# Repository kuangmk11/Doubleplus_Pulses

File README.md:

# Pulses Plus

A performance-oriented gate router for the Music Thing Turing Machine. Eight pulse channels,
each switchable to one of two merge buses or off; each bus computes the OR or the AND of
whatever is routed to it, chosen live from the panel.

**Built and tested.** 8 HP, 128.5 × 40.16 mm.

It sits **alongside** a stock Pulses expander rather than replacing it, taking its signals from
the Turing Machine's 16-pin expander ribbon and passing that ribbon through so other expanders
can still be chained downstream.

The stock Pulses gives you seven fixed outputs plus four hard-wired AND combinations. Those AND
outputs are the musical ones — ANDing two shift-register taps gives a sparser, related rhythm.
This generalises that: any subset of the eight bits, OR'd or AND'd, chosen by hand, live. The
four fixed ANDs become a strict subset of what the switches can do.

---

## What's here

| | |
|---|---|
| `pulses_plus_submin.kicad_sch` | schematic — 87 placed components |
| `pulses_plus_submin.kicad_pcb` | main board |
| **`pulses_plus_submin_panel_v4.kicad_pcb`** | **current panel** |
| `pulses_plus_submin_panel.kicad_pcb` | v1 panel — the geometry source `build_panel.py` inherits holes from |
| `pulses_plus_submin.pretty/` | project footprints — toggle, jack, LED, panel holes |
| `switch_fix.kicad_sym` | the DPDT symbol with the pin numbering the footprint expects |
| `3d/` | 3D models the footprints reference |
| `BOM.md` | bill of materials, DigiKey and JLCPCB/LCSC columns |
| `BOM_DigiKey.csv` | the same BOM as a DigiKey cart upload |
| `gerbers/` | fab packages — see below |
| `tools/build_panel.py` | regenerates the panel artwork |
| `PANEL_STYLE_v1.12.md` | the panel house style |
| `docs/pulses-plus-design.md` | full design write-up, including the diode-leak analysis and why 6 HP was abandoned |
| `docs/sw-t2-4x-b-a2-ma2-data-sheet.pdf` | Taiway 200-MDP3 toggle datasheet |

### Which gerbers to order

`gerbers/` accumulated every revision that was sent out. The panel to order is
`gerbers/panelv4.rar`. For the board:

- **`gerbers_v2/`** — current plot of `pulses_plus_submin_v2.kicad_pcb`, **including C5/C6**
  (see the erratum below). Not yet fabbed.
- **`gerbers/controlv2.zip`** — what was actually fabbed and built. Boards from this package
  predate C5/C6 and need the two-capacitor rework.

The loose `.gbr`/`.drl` files at the top of `gerbers/` are the most recent plot of the
main board and the v1/v2 panels, kept unzipped for inspection.

---

## Erratum — ghost triggers on edge-sensitive gate inputs

**Any board built without C5/C6 needs a two-capacitor rework.**

**Symptom.** On the step *after* a real trigger — a step where the bus should be silent — a
downstream envelope fires an extra time. The bus LED never visibly flashes, and the same envelope
behaves correctly on the Turing Machine's own pulse output and on a stock Pulses. A **Kassutronics
ASR** is the known case; the affected class is any gate input that triggers on the *rising edge* at
a low threshold (the ASR's fires from ~+1.2 V).

**Cause.** The Turing Machine's expander bits are `stage AND clock`, and the clock's rising edge
opens that AND before the shift register has finished shifting — so the ribbon briefly presents the
previous step's pattern. This module's two cascaded CD40106 Schmitt buffers then regenerate that
soft sub-µs bump into a sharp, near-full-amplitude micro-gate. Full analysis in
[`docs/pulses-plus-design.md`](docs/pulses-plus-design.md#stale-bit-glitch-and-edge-sensitive-gate-inputs).

**Fix.** Tack a **4.7 nF** ceramic on top of **R15**, and another on top of **R16**. Those 1206 pads
are already `BUSA_SEL`→GND and `BUSB_SEL`→GND on the back of the board, so there are no trace cuts,
no lifted pins, and it is fully reversible. Verified on hardware.

- **Do not use a smaller value.** 1 nF was measured insufficient; 2.2 nF computes marginal.
- **Multing the output is not a workaround.** It appears to help and then stops helping — cable
  capacitance is an order of magnitude too small to filter this.
- The fix is in the **v2** project files (`pulses_plus_submin_v2.*`) as C5/C6. The v1 files do not
  have it.

## How it works

Each channel's DPDT ON-OFF-ON toggle throws left to bus A, right to bus B, or centre for off.
Both poles are used: pole 1 carries only the OR diodes, pole 2 only the AND diodes. That
separation is the one non-obvious constraint in the design — sharing a pole leaks current
through the unselected bus and pins its OR net high.

Per bus, a second toggle picks OR, MUTE or AND. Both nets are computed continuously and in
parallel, so the mode switch only selects which one reaches the output buffer and the 32 merge
diodes never switch. Centre-off leaves the buffer input pulled low, which is the mute.

The **EXT** jack is switched (normalled): unplugged, buffered BIT8 feeds channel 8; plugged, an
external gate takes its place through a transistor and Schmitt stage that squares up whatever
amplitude arrives.

Full write-up: **[`docs/pulses-plus-design.md`](docs/pulses-plus-design.md)**.

## Using it

The two buses are **two independent reads of the same shift register**. Whatever either one
plays is built from the same eight bits on the same loop, so they cannot drift apart — but give
them different channels, or put one in AND and the other in OR, and they come out at different
densities. Related, never identical. Most of the musical mileage is in that gap.

### Gates on A, note changes on B

The patch this turned out to be best at, and not one it was designed for:

1. **OUT A → your envelope or VCA gate.** A few channels to bus A in **OR** — a busy,
   rhythmic gate stream.
2. **OUT B → a quantizer's trigger or sample input**, with the Turing Machine's CV output
   feeding that quantizer's CV input. A *different*, smaller set of channels to bus B, in
   **AND** for something sparser again.

The quantizer only samples when bus B fires, so the note is **held** across every gate bus A
produces in between. A melody moves on its own slow rhythm while the gates articulate
underneath — and because both rhythms are subsets of one register, the note changes land on
beats the gate pattern already stresses. It reads as a phrase, not as two voices running at
once.

Being a Turing Machine underneath, the loop-length and randomness controls then act on the
whole thing at once: lock the register for a repeating riff, open it a crack and the melody
mutates while staying in its scale.

**Pulse width passes straight through.** The board is purely combinational: it merges what
arrives on the ribbon and never looks at the clock. It does not need to — the Turing Machine's
expander bus already carries each bit ANDed with the clock, so the bits arrive as *pulses*, and
the diode merge preserves their width. Feed the TM a narrow clock and the outputs are narrow;
feed it a wide one and they are wide, all the way to OUT A and OUT B.

So an AND that is true on three consecutive steps gives three pulses, one per step — each
re-triggering the envelope or re-pinging the quantizer, rather than merging into one long gate.
The note changes on every step the condition holds, which is why choosing a condition that comes
true *rarely* is what makes the melody move slowly.

**Things to reach for:**

- **B in AND with two or three channels** is the sweet spot. AND of several bits comes true
  rarely, which is what you want from a melody that moves every few bars rather than every step.
- **MUTE on B** freezes the pitch without touching the gate pattern — drop the melody in and
  out by hand mid-take. That is what the centre position is for.
- **The EXT jack earns its keep here.** Patch an outside rhythm into channel 8 and AND it into
  bus B, and the note only changes where your own pattern and the Turing Machine agree —
  a melody keyed to something the TM knows nothing about.
- An **AND bus with nothing routed to it sits high**, held there by its 10k pull-up rather than
  driven by any bit, so it never pings anything. Route at least one channel to a bus you want
  triggers from.

## Key parts

10 × Taiway 200-MDP3 sub-miniature DPDT ON-OFF-ON toggles (ø4.95 bushing), 2 × CD4050 buffers,
1 × CD40106 Schmitt, 33 × 1N4148, 10 × 3 mm LEDs, 3 × Thonkiconn jacks — **J3 must be the
switched variant** — and 2 × 2×8 IDC headers for ribbon in and thru. See [`BOM.md`](BOM.md).

---

## Panel

The current panel is **v4**, `pulses_plus_submin_panel_v4.kicad_pcb` — white silkscreen on black
soldermask, drawn to [`PANEL_STYLE_v1.12.md`](PANEL_STYLE_v1.12.md).

It is generated. [`tools/build_panel.py`](tools/build_panel.py) reads the v1 panel and regenerates
only the artwork, inheriting every control-hole position, so the style guide's one non-negotiable
rule — hole positions are inherited, never computed — holds by construction rather than by
inspection:

```sh
python3 tools/build_panel.py
```

Mounting is four 6.4 × 3.2 mm obround slots on Edge.Cuts, horizontal for ±1.6 mm of slide.
`kicad-cli pcb drc` reports zero violations. Zones refill on open — refill before plotting.

Reading the panel: a ring means signal leaves there, so the two output jacks are the only closed
circles. `A`/`B` beside each toggle are throw directions, not names. The mode stack is `AND` up,
`MUTE` centre, `OR` down. Names sit below the thing they name.

---

## Related repositories

- **[Doubleplus_Pulses_VCV](https://github.com/kuangmk11/Doubleplus_Pulses_VCV)** — a VCV Rack 2 port
  of this module. It reconstructs the Turing Machine's shift register locally, so it runs without
  the hardware.
- **[Turing-Pulse-Expander](https://github.com/kuangmk11/Turing-Pulse-Expander)** — the archive:
  Tom Whitwell's original Rev 2 expander, plus the superseded studies this design grew out of.

## Licence

CC BY-NC-SA 4.0 — see [`LICENSE`](LICENSE).

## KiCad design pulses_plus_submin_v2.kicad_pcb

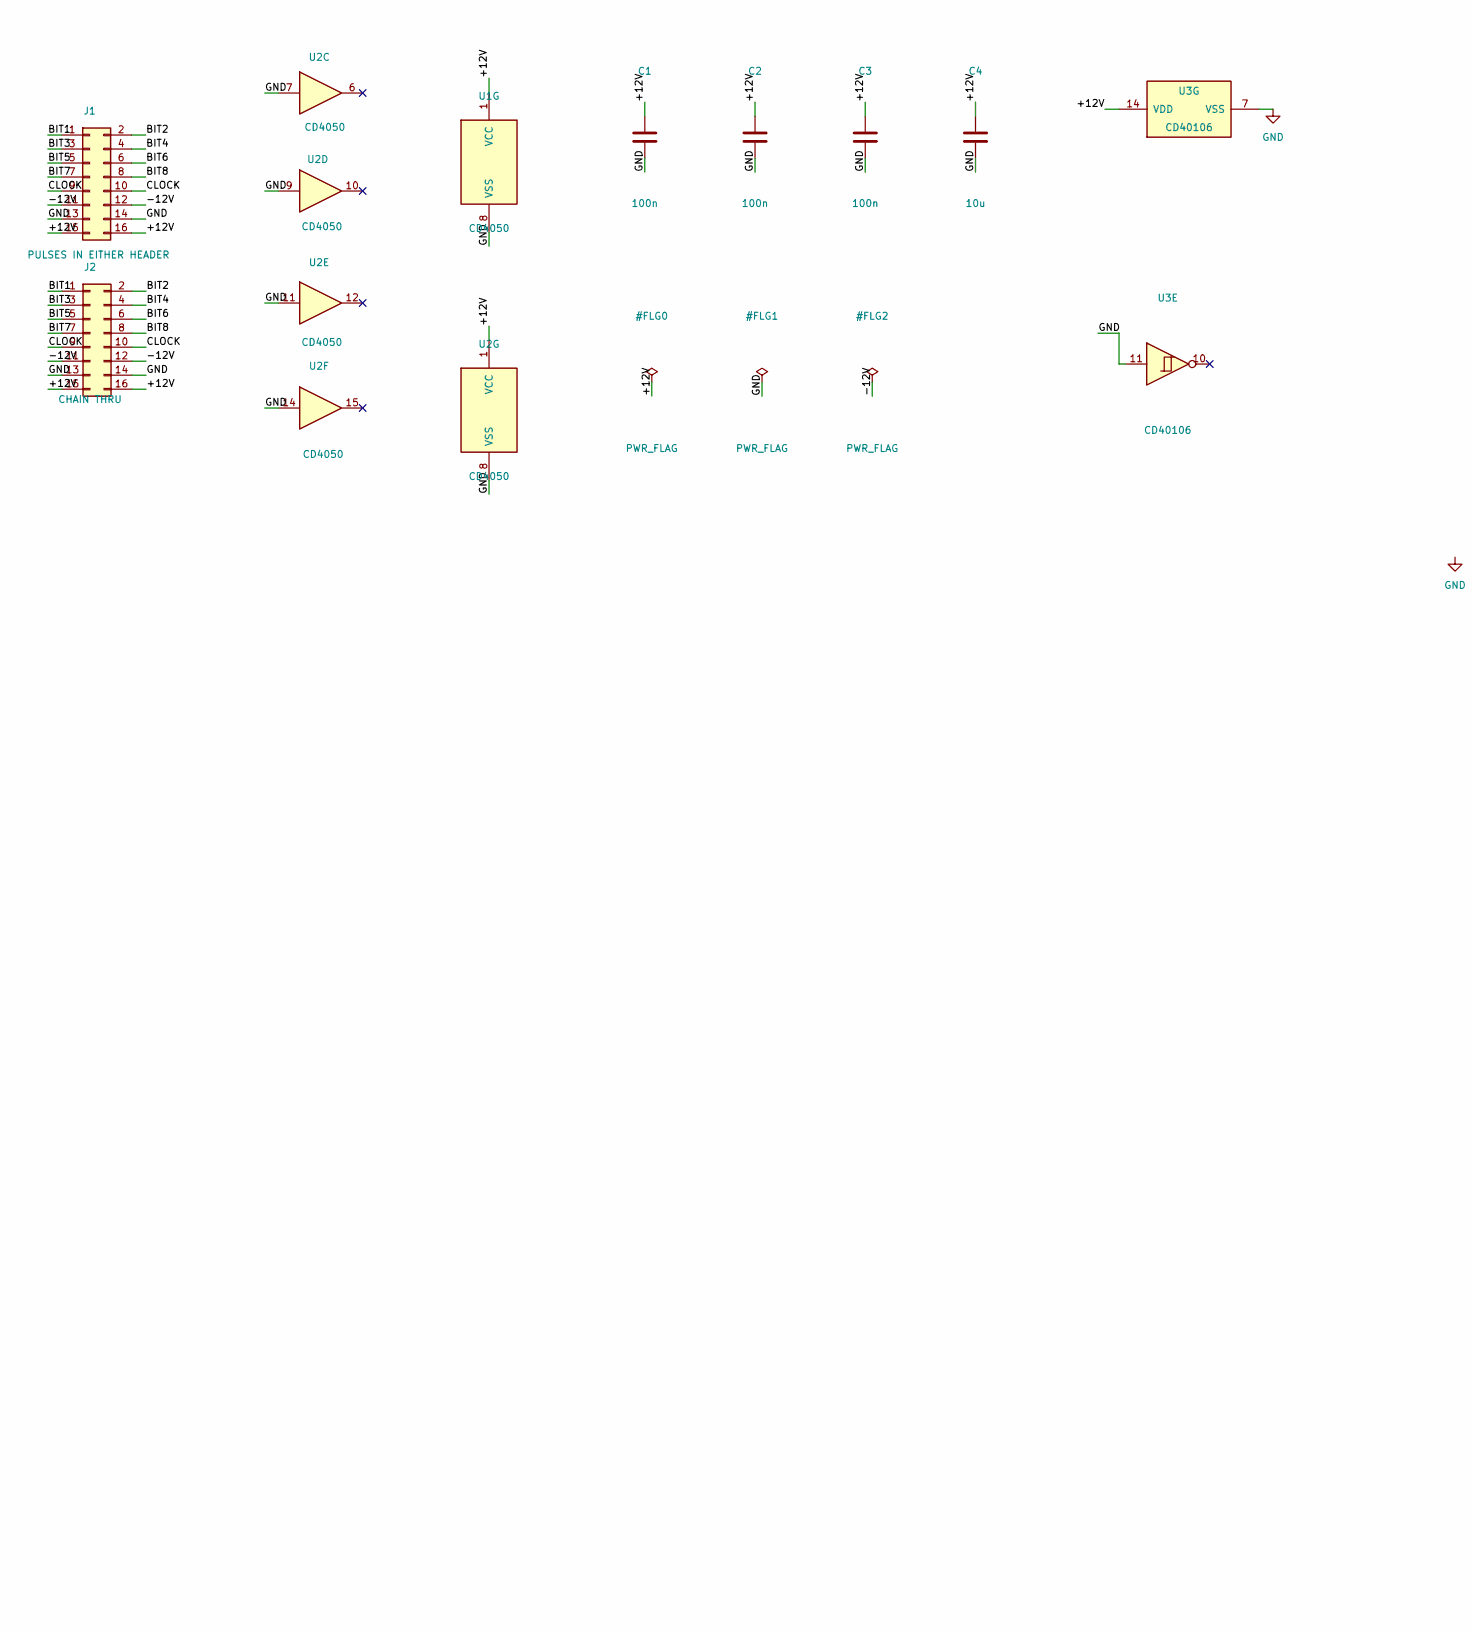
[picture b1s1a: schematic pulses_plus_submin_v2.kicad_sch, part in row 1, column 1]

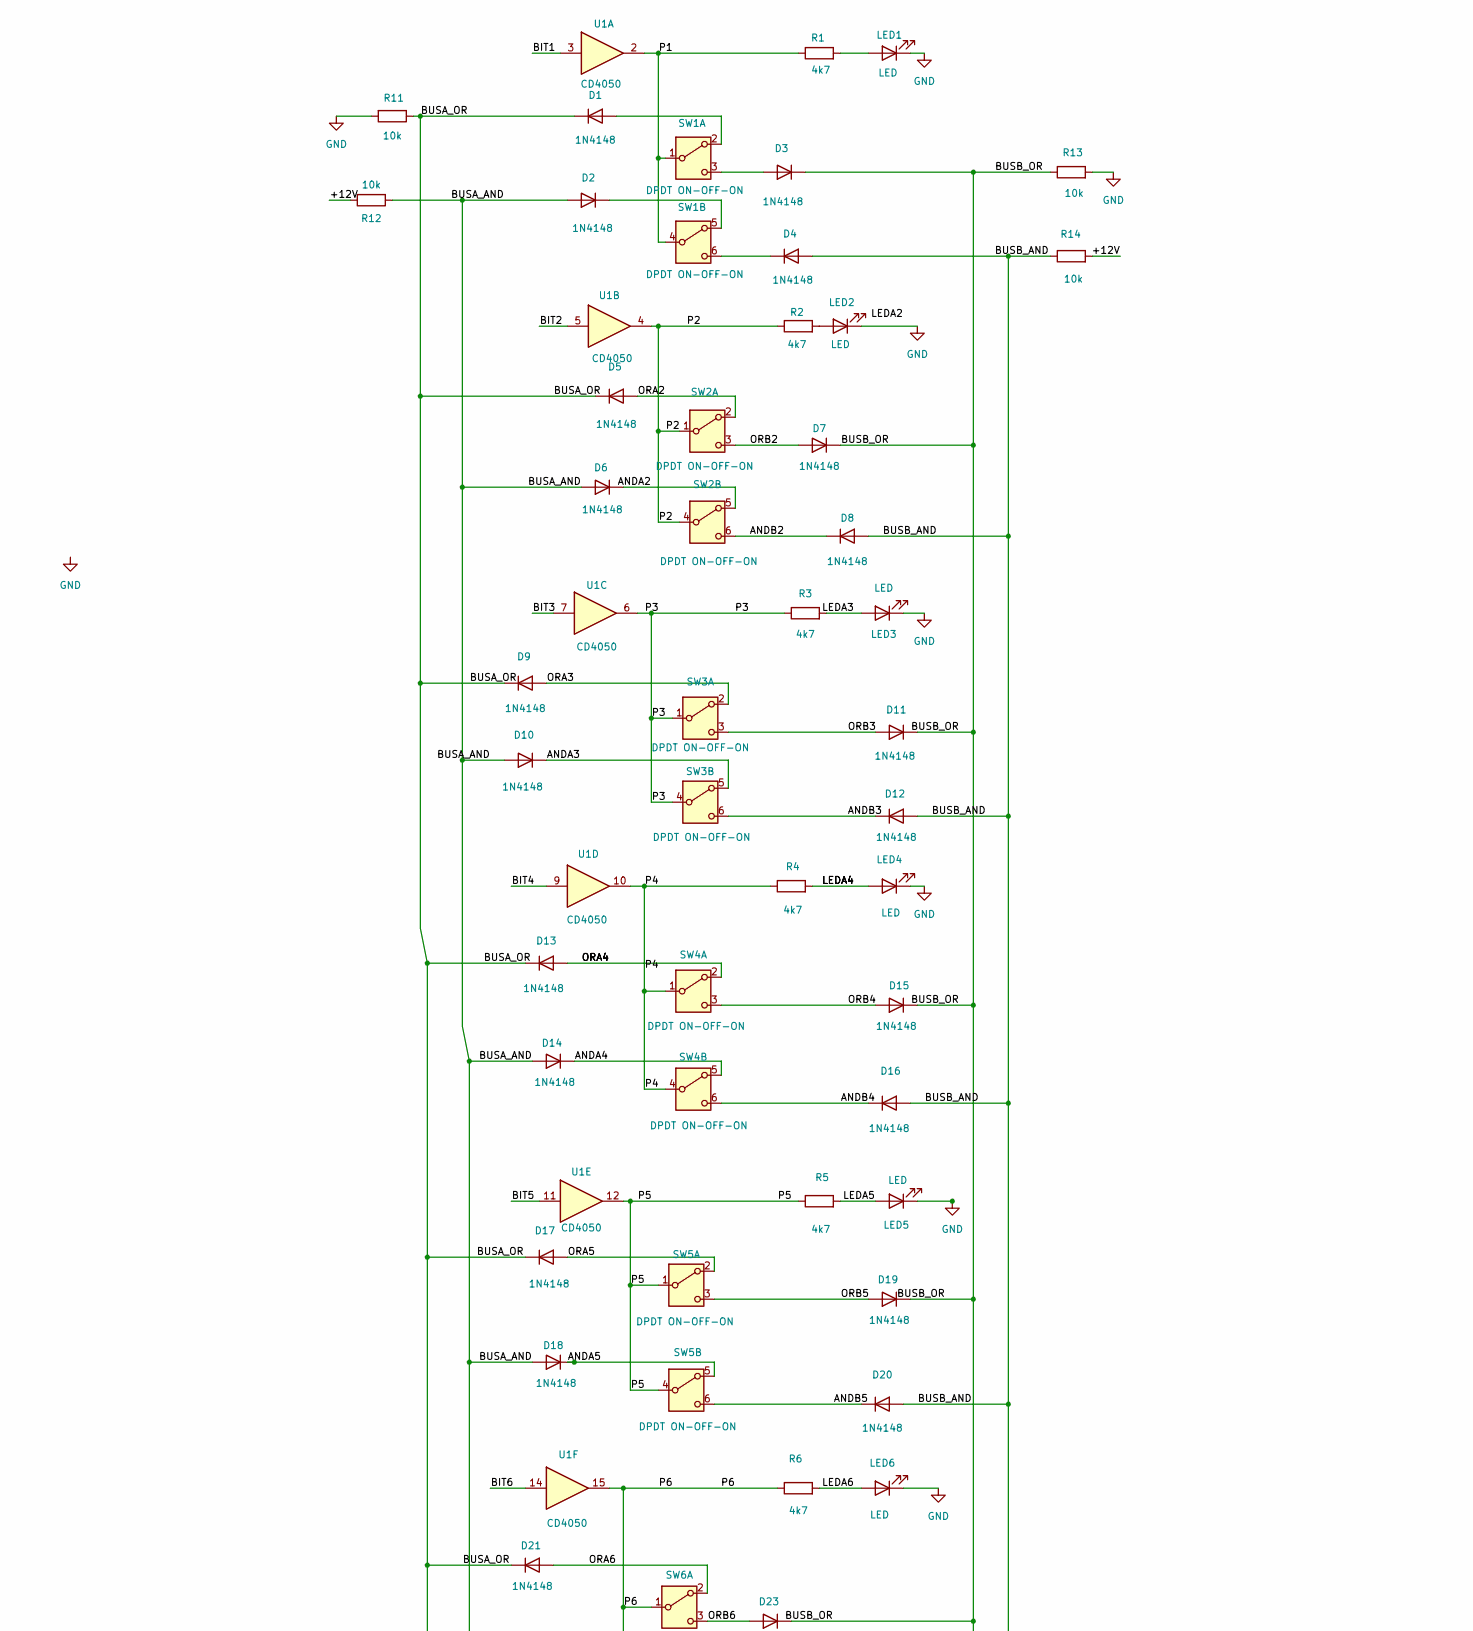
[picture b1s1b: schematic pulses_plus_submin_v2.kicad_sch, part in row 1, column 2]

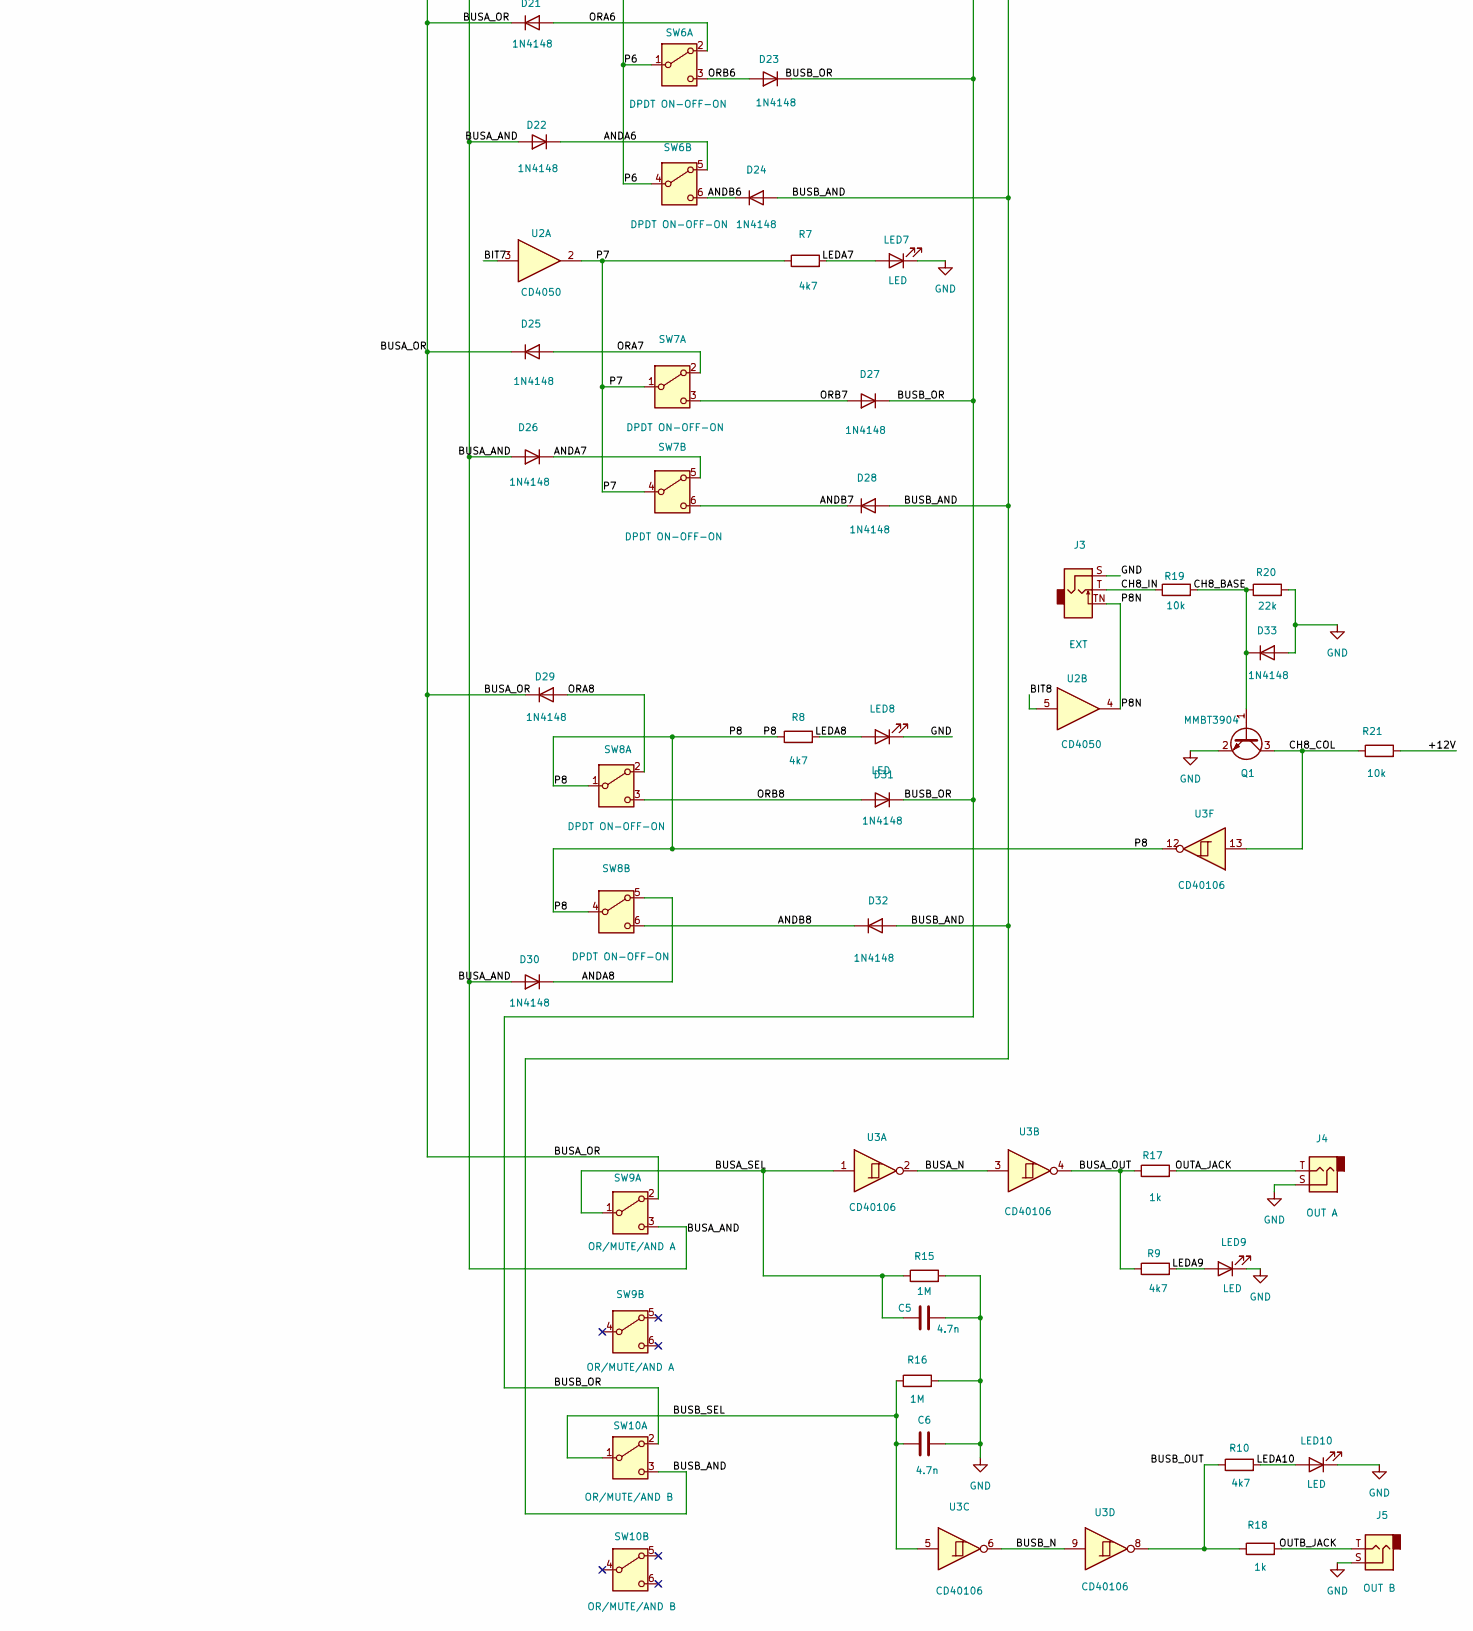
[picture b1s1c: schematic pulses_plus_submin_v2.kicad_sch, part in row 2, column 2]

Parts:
C1, C2, C3: 100n; C_1206_3216Metric_Pad1.33x1.80mm_HandSolder
C4: 10u; C_1206_3216Metric_Pad1.33x1.80mm_HandSolder
C5, C6: 4.7n; C_1206_3216Metric_Pad1.33x1.80mm_HandSolder
D1, D2, D3, D4, D5, D6, D7, D8, D9, D10, D11, D12, D13, D14, D15, D16, D17, D18, D19, D20, D21, D22, D23, D24, D25, D26, D27, D28, D29, D30, D31, D32, D33: 1N4148; D_SOD-123
J1: PULSES IN EITHER HEADER; IDC-Header_2x08_P2.54mm_Vertical
J2: CHAIN THRU; IDC-Header_2x08_P2.54mm_Vertical
J3: EXT; Thonkiconn_PJ301M
J4: OUT A; Thonkiconn_PJ301M
J5: OUT B; Thonkiconn_PJ301M
LED1, LED2, LED3, LED4, LED5, LED6, LED7, LED8, LED9, LED10: LED; LED_D3.0mm
Q1: MMBT3904; SOT-23
R1, R2, R3, R4, R5, R6, R7, R8, R9, R10: 4k7; R_1206_3216Metric_Pad1.30x1.75mm_HandSolder
R11, R12, R13, R14, R19, R21: 10k; R_1206_3216Metric_Pad1.30x1.75mm_HandSolder
R15, R16: 1M; R_1206_3216Metric_Pad1.30x1.75mm_HandSolder
R17, R18: 1k; R_1206_3216Metric_Pad1.30x1.75mm_HandSolder
R20: 22k; R_1206_3216Metric_Pad1.30x1.75mm_HandSolder
SW1, SW2, SW3, SW4, SW5, SW6, SW7, SW8: DPDT ON-OFF-ON; SW_200_MDP3_DPDT
SW9: OR/MUTE/AND A; SW_200_MDP3_DPDT
SW10: OR/MUTE/AND B; SW_200_MDP3_DPDT
U1, U2: CD4050; DIP-16_W7.62mm
U3: CD40106; DIP-14_W7.62mm

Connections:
/+12V: C1.1, C2.1, C3.1, C4.1, J1.15, J1.16, J2.15, J2.16, R12.2, R14.2, R21.2, U1.1 (VCC), U2.1 (VCC), U3.14 (VDD)
/-12V: J1.11, J1.12, J2.11, J2.12
/ANDA2: D6.1 (K), SW2.5 (B)
/ANDA3: D10.1 (K), SW3.5 (B)
/ANDA4: D14.1 (K), SW4.5 (B)
/ANDA5: D18.1 (K), SW5.5 (B)
/ANDA6: D22.1 (K), SW6.5 (B)
/ANDA7: D26.1 (K), SW7.5 (B)
/ANDA8: D30.1 (K), SW8.5 (B)
/ANDB2: D8.1 (K), SW2.6 (C)
/ANDB3: D12.1 (K), SW3.6 (C)
/ANDB4: D16.1 (K), SW4.6 (C)
/ANDB5: D20.1 (K), SW5.6 (C)
/ANDB6: D24.1 (K), SW6.6 (C)
/ANDB7: D28.1 (K), SW7.6 (C)
/ANDB8: D32.1 (K), SW8.6 (C)
/BIT1: J1.1, J2.1, U1.3
/BIT2: J1.2, J2.2, U1.5
/BIT3: J1.3, J2.3, U1.7
/BIT4: J1.4, J2.4, U1.9
/BIT5: J1.5, J2.5, U1.11
/BIT6: J1.6, J2.6, U1.14
/BIT7: J1.7, J2.7, U2.3
/BIT8: J1.8, J2.8, U2.5
/BUSA_AND: D2.2 (A), D6.2 (A), D10.2 (A), D14.2 (A), D18.2 (A), D22.2 (A), D26.2 (A), D30.2 (A), R12.1, SW9.3 (C)
/BUSA_N: U3.2, U3.3
/BUSA_OR: D1.1 (K), D5.1 (K), D9.1 (K), D13.1 (K), D17.1 (K), D21.1 (K), D25.1 (K), D29.1 (K), R11.1, SW9.2 (B)
/BUSA_OUT: R9.1, R17.1, U3.4
/BUSB_AND: D4.2 (A), D8.2 (A), D12.2 (A), D16.2 (A), D20.2 (A), D24.2 (A), D28.2 (A), D32.2 (A), R14.1, SW10.3 (C)
/BUSB_N: U3.6, U3.9
/BUSB_OR: D3.1 (K), D7.1 (K), D11.1 (K), D15.1 (K), D19.1 (K), D23.1 (K), D27.1 (K), D31.1 (K), R13.1, SW10.2 (B)
/BUSB_OUT: R10.1, R18.1, U3.8
/CH8_BASE: D33.1 (K), Q1.1 (B), R19.2, R20.1
/CH8_COL: Q1.3 (C), R21.1, U3.13
/CH8_IN: J3.T, R19.1
/CLOCK: J1.9, J1.10, J2.9, J2.10
/LEDA3: LED3.2 (A), R3.2
/LEDA5: LED5.2 (A), R5.2
/LEDA6: LED6.2 (A), R6.2
/LEDA7: LED7.2 (A), R7.2
/LEDA8: LED8.2 (A), R8.2
/LEDA9: LED9.2 (A), R9.2
/LEDA10: LED10.2 (A), R10.2
/ORA2: D5.2 (A), SW2.2 (B)
/ORA3: D9.2 (A), SW3.2 (B)
/ORA5: D17.2 (A), SW5.2 (B)
/ORA6: D21.2 (A), SW6.2 (B)
/ORA7: D25.2 (A), SW7.2 (B)
/ORA8: D29.2 (A), SW8.2 (B)
/ORB2: D7.2 (A), SW2.3 (C)
/ORB3: D11.2 (A), SW3.3 (C)
/ORB4: D15.2 (A), SW4.3 (C)
/ORB5: D19.2 (A), SW5.3 (C)
/ORB6: D23.2 (A), SW6.3 (C)
/ORB7: D27.2 (A), SW7.3 (C)
/ORB8: D31.2 (A), SW8.3 (C)
/OUTA_JACK: J4.T, R17.2
/OUTB_JACK: J5.T, R18.2
/P1: R1.1, SW1.1 (A), SW1.4 (A), U1.2
/P2: R2.1, SW2.1 (A), SW2.4 (A), U1.4
/P3: R3.1, SW3.1 (A), SW3.4 (A), U1.6
/P4: R4.1, SW4.1 (A), SW4.4 (A), U1.10
/P5: R5.1, SW5.1 (A), SW5.4 (A), U1.12
/P6: R6.1, SW6.1 (A), SW6.4 (A), U1.15
/P7: R7.1, SW7.1 (A), SW7.4 (A), U2.2
/P8: R8.1, SW8.1 (A), SW8.4 (A), U3.12
/P8N: J3.TN, U2.4
GND: C1.2, C2.2, C3.2, C4.2, C5.2, C6.2, D33.2 (A), J1.13, J1.14, J2.13, J2.14, J3.S, J4.S, J5.S, LED1.1 (K), LED2.1 (K), LED3.1 (K), LED4.1 (K), LED5.1 (K), LED6.1 (K), LED7.1 (K), LED8.1 (K), LED9.1 (K), LED10.1 (K), Q1.2 (E), R11.2, R13.2, R15.2, R16.2, R20.2, U1.8 (VSS), U2.7, U2.8 (VSS), U2.9, U2.11, U2.14, U3.7 (VSS), U3.11
unnamed: D1.2 (A), SW1.2 (B)
unnamed: D2.1 (K), SW1.5 (B)
unnamed: D3.2 (A), SW1.3 (C)
unnamed: D4.1 (K), SW1.6 (C)
unnamed: D13.2 (A), SW4.2 (B)
unnamed: LED1.2 (A), R1.2
unnamed: LED2.2 (A), R2.2
unnamed: LED4.2 (A), R4.2

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
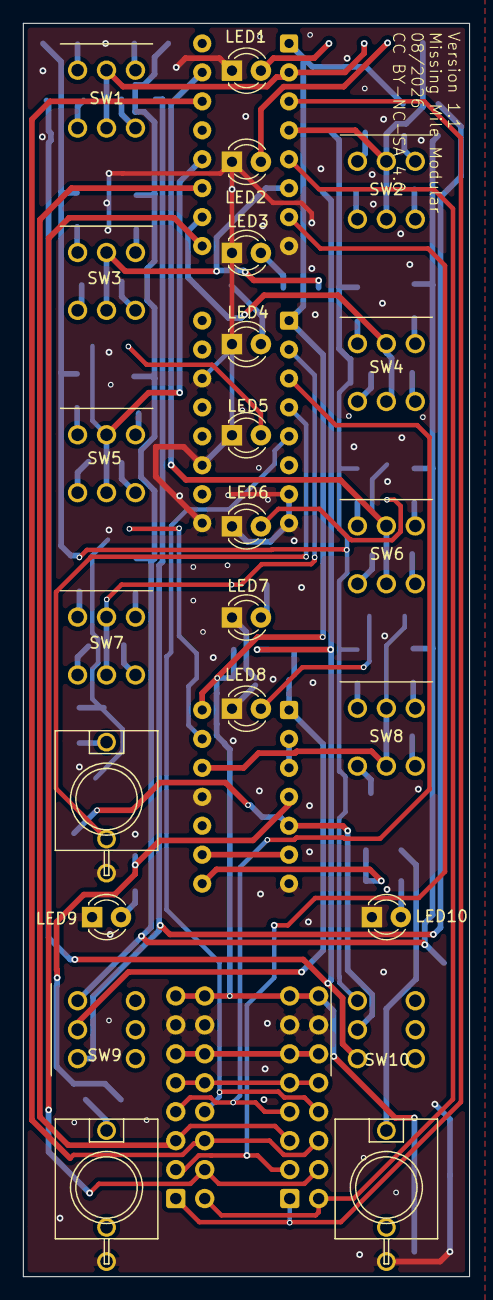
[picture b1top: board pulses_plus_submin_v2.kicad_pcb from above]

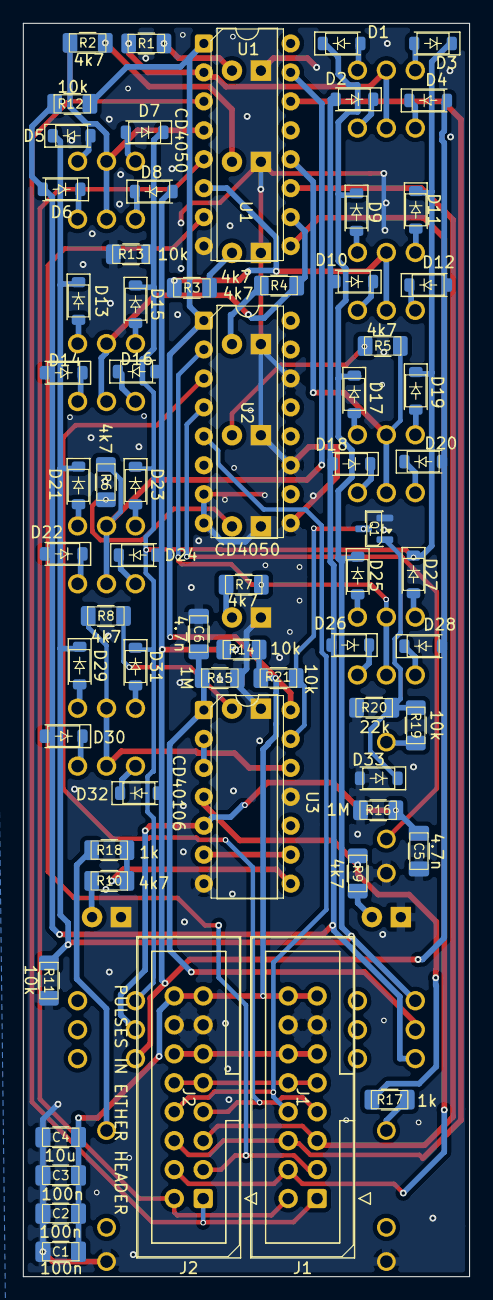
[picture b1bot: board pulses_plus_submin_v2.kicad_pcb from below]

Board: 2 copper layers, 39.2 x 110.0 mm, 89 parts (66 on the bottom side), 78 nets.

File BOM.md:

# Pulses Plus (sub-mini) — Bill of Materials

Generated from `pulses_plus_submin_v2.kicad_sch` (89 placed components, 19 line items).
Two sourcing columns:

- **DigiKey** — for hand assembly (the THT parts and jacks are hand-solder anyway).
- **JLCPCB / LCSC** — the LCSC `C`-number is what JLCPCB SMT assembly needs for the SMD parts.

Switches are sourced from **Love My Switches** (they are the Taiway 200 sub-mini toggles,
not a DigiKey/LCSC stock part).

> ⚠ **Verify before ordering** — part numbers marked *(verify)* are the correct manufacturer
> series but the exact distributor SKU / LCSC stock C-number should be confirmed against live
> stock at order time. Confirmed numbers came from distributor listings and are noted as such.

---

## BOM table

| # | Qty | Value | Refs | Package / Footprint | Mfr Part | DigiKey | JLCPCB / LCSC |
|---|-----|-------|------|---------------------|----------|---------|---------------|
| 1 | 10 | **DPDT ON-OFF-ON toggle** | SW1–SW10 | Taiway 200 sub-mini, PC vertical, ø4.95 bushing | Taiway **200-MDP3-T2B1M2QE** | — | — |
| 2 | 2 | CD4050 hex buffer | U1, U2 | DIP-16 | **CD4050BE** (TI) | 296-2056-ND | C(verify) |
| 3 | 1 | CD40106 hex Schmitt | U3 | DIP-14 | **CD40106BE** (TI) | 296-9797-5-ND *(verify)* | **C71251** |
| 4 | 1 | MMBT3904 NPN | Q1 | SOT-23 | **MMBT3904** | MMBT3904FSCT-ND | **C20526** |
| 5 | 33 | 1N4148 switching diode | D1–D33 | SOD-123 (`Diode_SMD:D_SOD-123`) | **1N4148W** | 1N4148W-FDICT-ND | **C81598** |
| 6 | 10 | 4k7 resistor | R1–R10 | 1206, 1% | Yageo **RC1206FR-074K7L** | search mfr PN | C(verify) |
| 7 | 6 | 10k resistor | R11–R14, R19, R21 | 1206, 1% | Yageo **RC1206FR-0710KL** | search mfr PN | C(verify) |
| 8 | 2 | 1k resistor | R17, R18 | 1206, 1% | Yageo **RC1206FR-071KL** | search mfr PN | C(verify) |
| 9 | 1 | 22k resistor | R20 | 1206, 1% | Yageo **RC1206FR-0722KL** | search mfr PN | C(verify) |
| 10 | 2 | 1M resistor | R15, R16 | 1206, 1% | Yageo **RC1206FR-071ML** | search mfr PN | C(verify) |
| 11 | 3 | 100n capacitor | C1, C2, C3 | 1206, X7R, 50V | Samsung **CL31B104KBCNNNC** | 1276-1092-1-ND *(verify)* | C(verify) |
| 12 | 1 | 10µ capacitor | C4 | 1206, X5R, 25V | Samsung **CL31A106KBHNNNE** | 1276-1940-1-ND *(verify)* | C(verify) |
| 13 | 10 | 3mm LED, high-brightness | LED1–LED10 | 3mm THT | e.g. Kingbright WP710A10 series | any 3mm LED | — |
| 14 | 3 | 3.5mm mono jack "Thonkiconn" | J3 (EXT, switched), J4 (OUT A), J5 (OUT B) | PJ301M-12 / PJ398SM | **PJ398SM** | not stocked | not stocked |
| 15 | 2 | 2×8 IDC box header, 2.54mm | J1 (PULSES IN), J2 (CHAIN THRU) | shrouded, vertical | generic 2x8 IDC | 2×8 shrouded header | C(verify) |
| 16 | 2 | **4.7n capacitor** | C5, C6 | 1206, X7R, 50V | Samsung **CL31B472KBCNNNC** *(verify)* | search mfr PN | C(verify) |

**C5/C6 are the glitch filter** — 4.7 nF from each mode-switch common (`BUSA_SEL` / `BUSB_SEL`)
to GND, sitting across R15/R16. They are not decoupling and not optional: without them the module
passes a sub-µs stale-bit spike from the Turing Machine's expander bus through its Schmitt output
buffers, which false-triggers edge-sensitive gate inputs (a Kassutronics ASR is the known case).
**Do not substitute 1 n or 2.2 n** — 1 n was measured insufficient and 2.2 n computes marginal. See
the design doc's *Stale-bit glitch* section.

**J3 must be the switched (normalling) variant** — its break contact normals buffered BIT8 into
channel 8. J4/J5 are plain mono. All three are the same Thonkiconn body.

---

## Sourcing notes

**Switches (SW1–SW10) — Love My Switches**
Taiway **200-MDP3-T2B1M2QE**, "Sub-Mini DPDT On-Off-On, PCB Mount, Short Shaft."
~$2.15 ea (≈ $21.50 for 10). Body 8.1 × 23.2 mm, ships with two nuts + a washer.
Product page: <https://lovemyswitches.com/taiway-sub-mini-dpdt-on-off-on-sw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
Panel hole is ø4.95 mm (10-48 UNS bushing). All 10 switches are this one part.

**Thonkiconn jacks (J3/J4/J5)** — not a DigiKey/LCSC catalog part. Buy from Thonk, Love My
Switches, Synthrotek, or Oddvolt (PJ398SM / PJ301M-12; the two are interchangeable). If you want
JLCPCB to place them, you'll need to supply them as a consigned part or substitute a catalog jack
with the same footprint.

**Resistors** — Yageo RC1206 series part numbers above are deterministic (`RC1206FR-07` + value
code + `L`, F = 1%). Any 1206 thick-film at 1% is fine; values are non-critical. On JLCPCB these
are Basic parts — pick the in-stock C-number for each value in the parts tool.

**Ceramics** — 100n/10µ 1206 X7R/X5R; any reputable 1206 MLCC works. The Samsung CL31 series
numbers are representative JLCPCB Basic parts.

---

## Action items before fab

1. **Diode footprint — RESOLVED in the v2 project.** All 33 diodes (D1–D33) are on
   `Diode_SMD:D_SOD-123`, part **1N4148W / C81598 / DK 1N4148W-FDICT-ND**, in *both*
   `pulses_plus_submin_v2.kicad_sch` and `pulses_plus_submin_v2.kicad_pcb` — verified by inspection,
   so *Update PCB from Schematic* no longer reverts them to 1206. Nets intact (8 diodes per bus,
   pad 1 = K → bus/GND, pad 2 = A).
   > ⚠ The **v1** files (`pulses_plus_submin.kicad_sch`) still carry the old 1206 footprint fields.
   > Work in the v2 project.

2. **Meter the switch** — confirm centre pin = common on the actual Taiway part before committing
   to a board run (design open-question #1). Everything assumes centre-is-common.

3. **LED polarity/brightness** — footprint pad 1 = cathode → GND, pad 2 = anode → 4k7. Use
   modern high-brightness 3mm LEDs (drive is only ~2 mA through 4k7 from a CD4050 output at 12 V).

---

## Verified vs. representative

| Confirmed from distributor listings | Representative (confirm at order) |
|---|---|
| Taiway 200-MDP3-T2B1M2QE (Love My Switches) | CD4050BE LCSC C-number |
| CD4050BE — DigiKey 296-2056-ND | CD40106BE DigiKey SKU |
| CD40106BE — LCSC C71251 | all passive LCSC C-numbers |
| MMBT3904 — LCSC C20526 | ceramic cap DigiKey SKUs |
| 1N4148W — LCSC C81598, DigiKey 1N4148W-FDICT-ND | LED / IDC header specifics |
